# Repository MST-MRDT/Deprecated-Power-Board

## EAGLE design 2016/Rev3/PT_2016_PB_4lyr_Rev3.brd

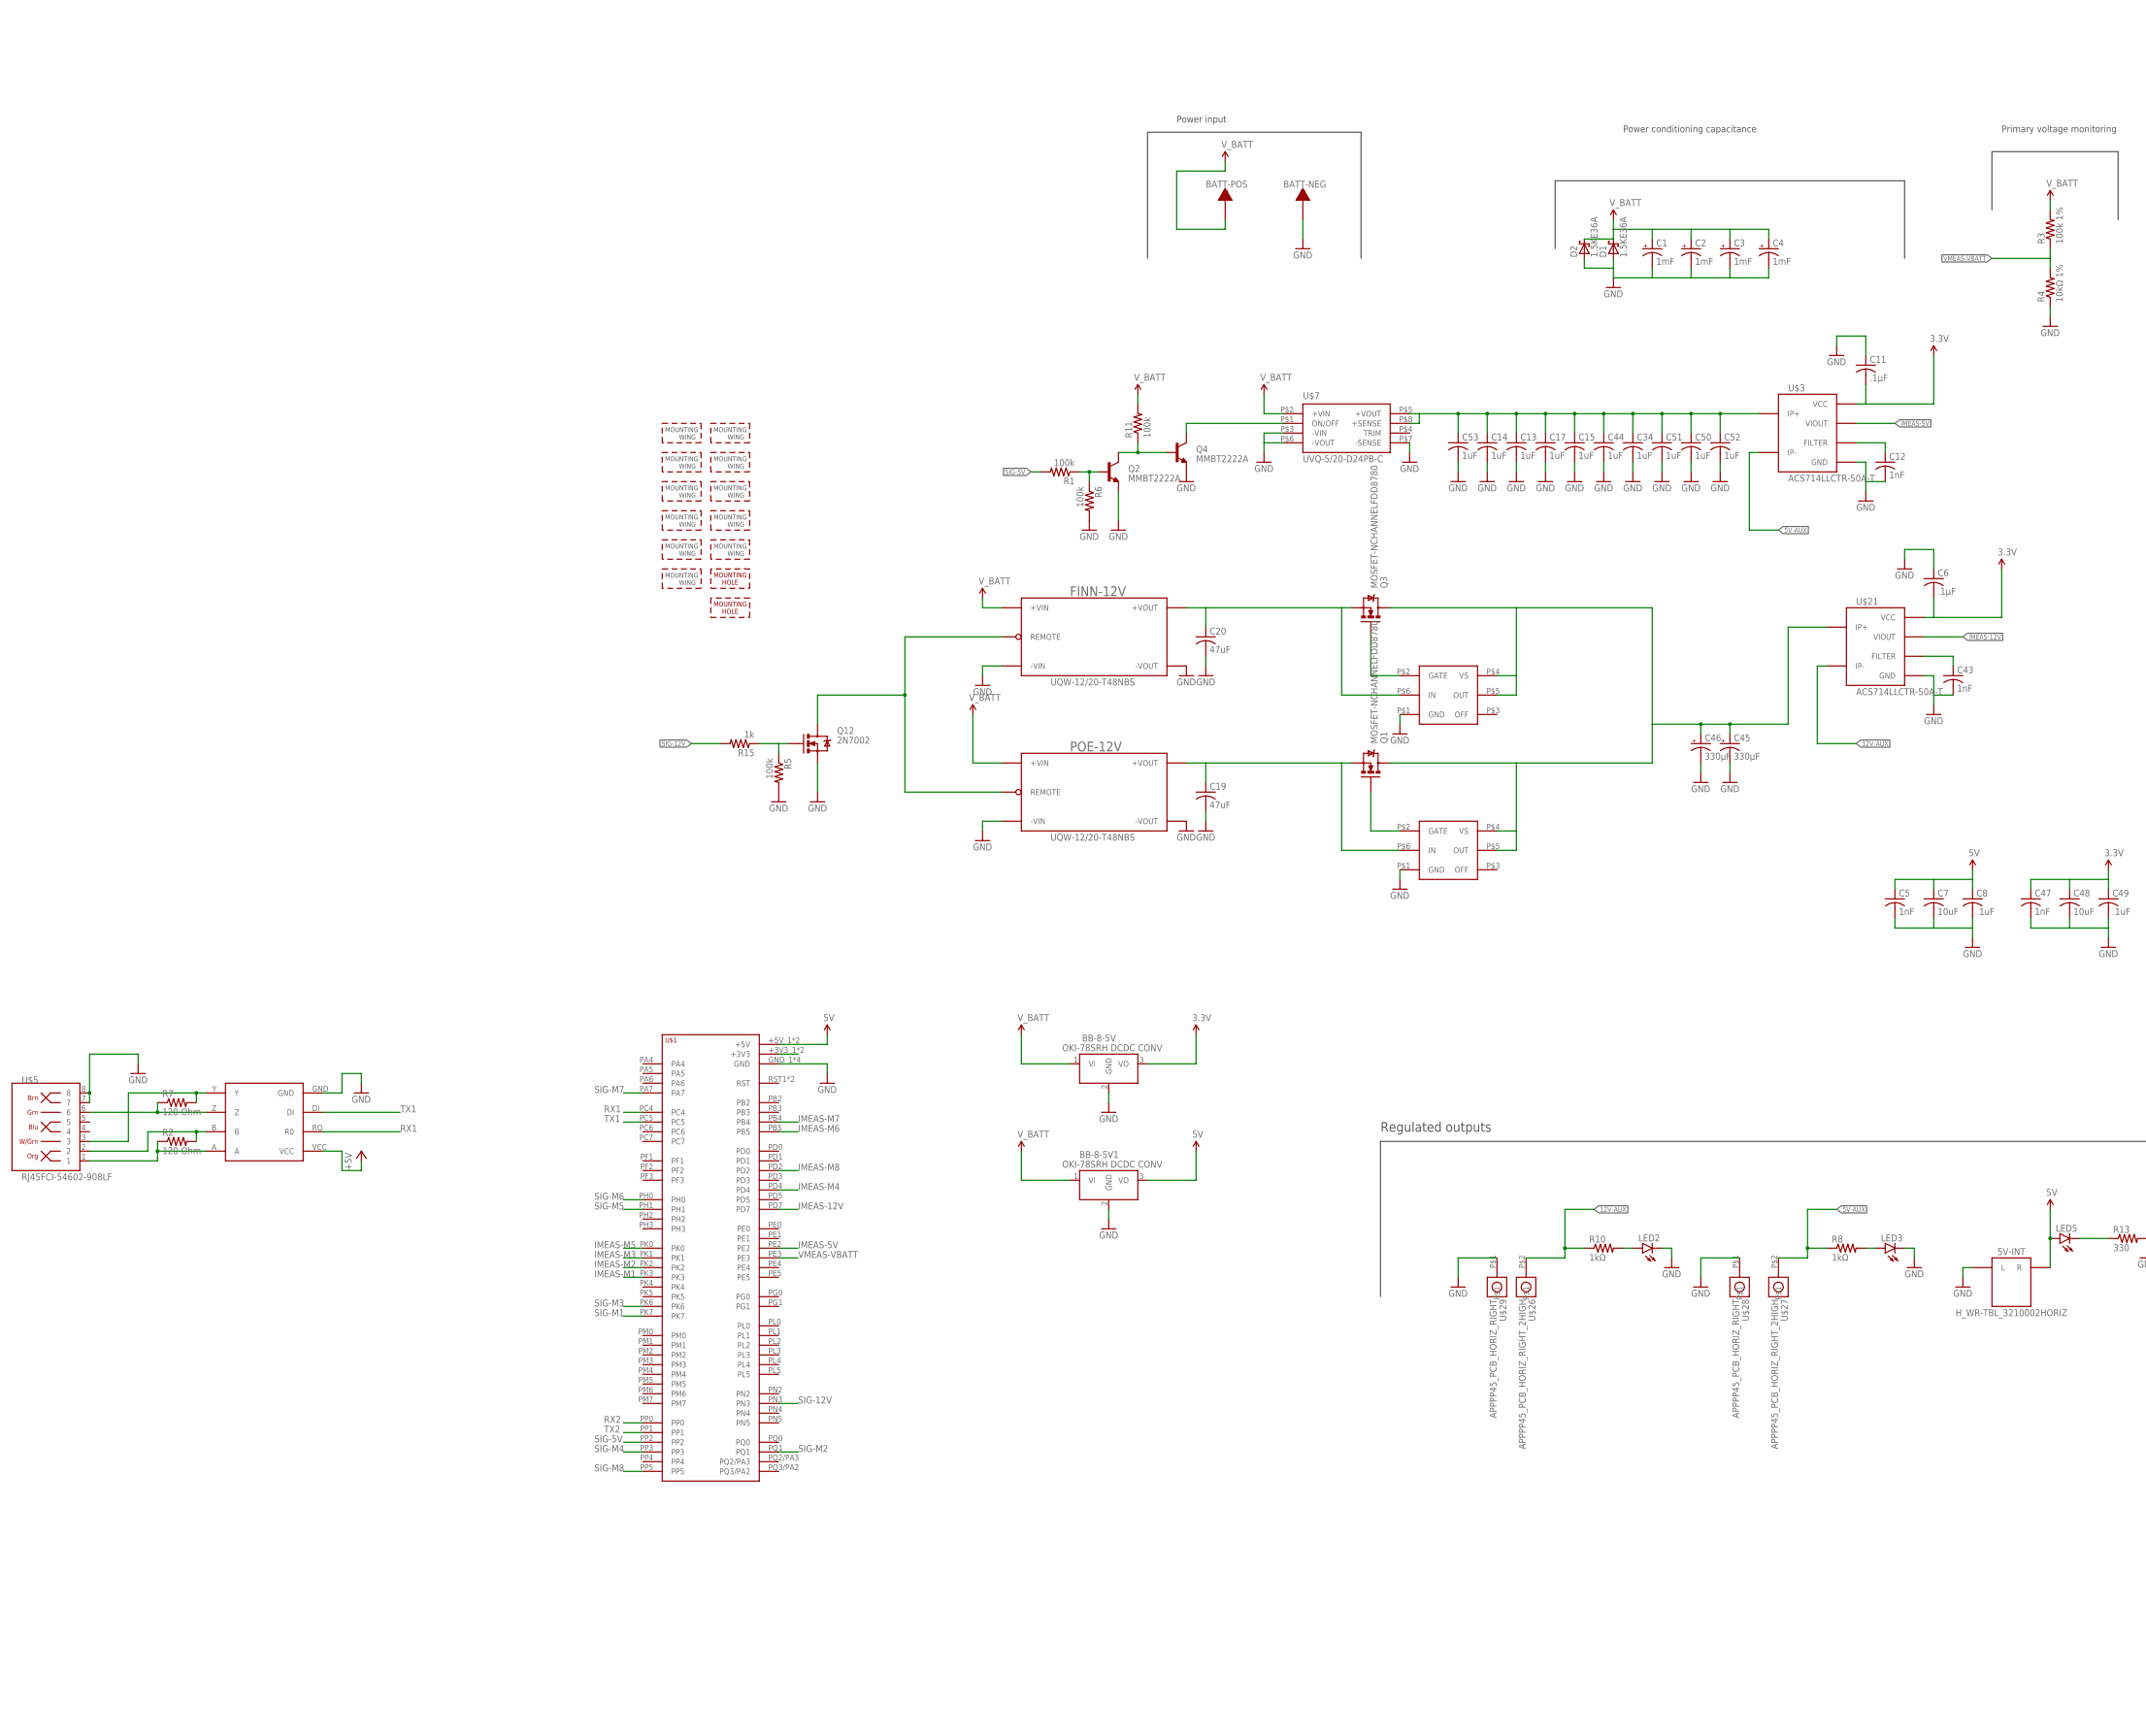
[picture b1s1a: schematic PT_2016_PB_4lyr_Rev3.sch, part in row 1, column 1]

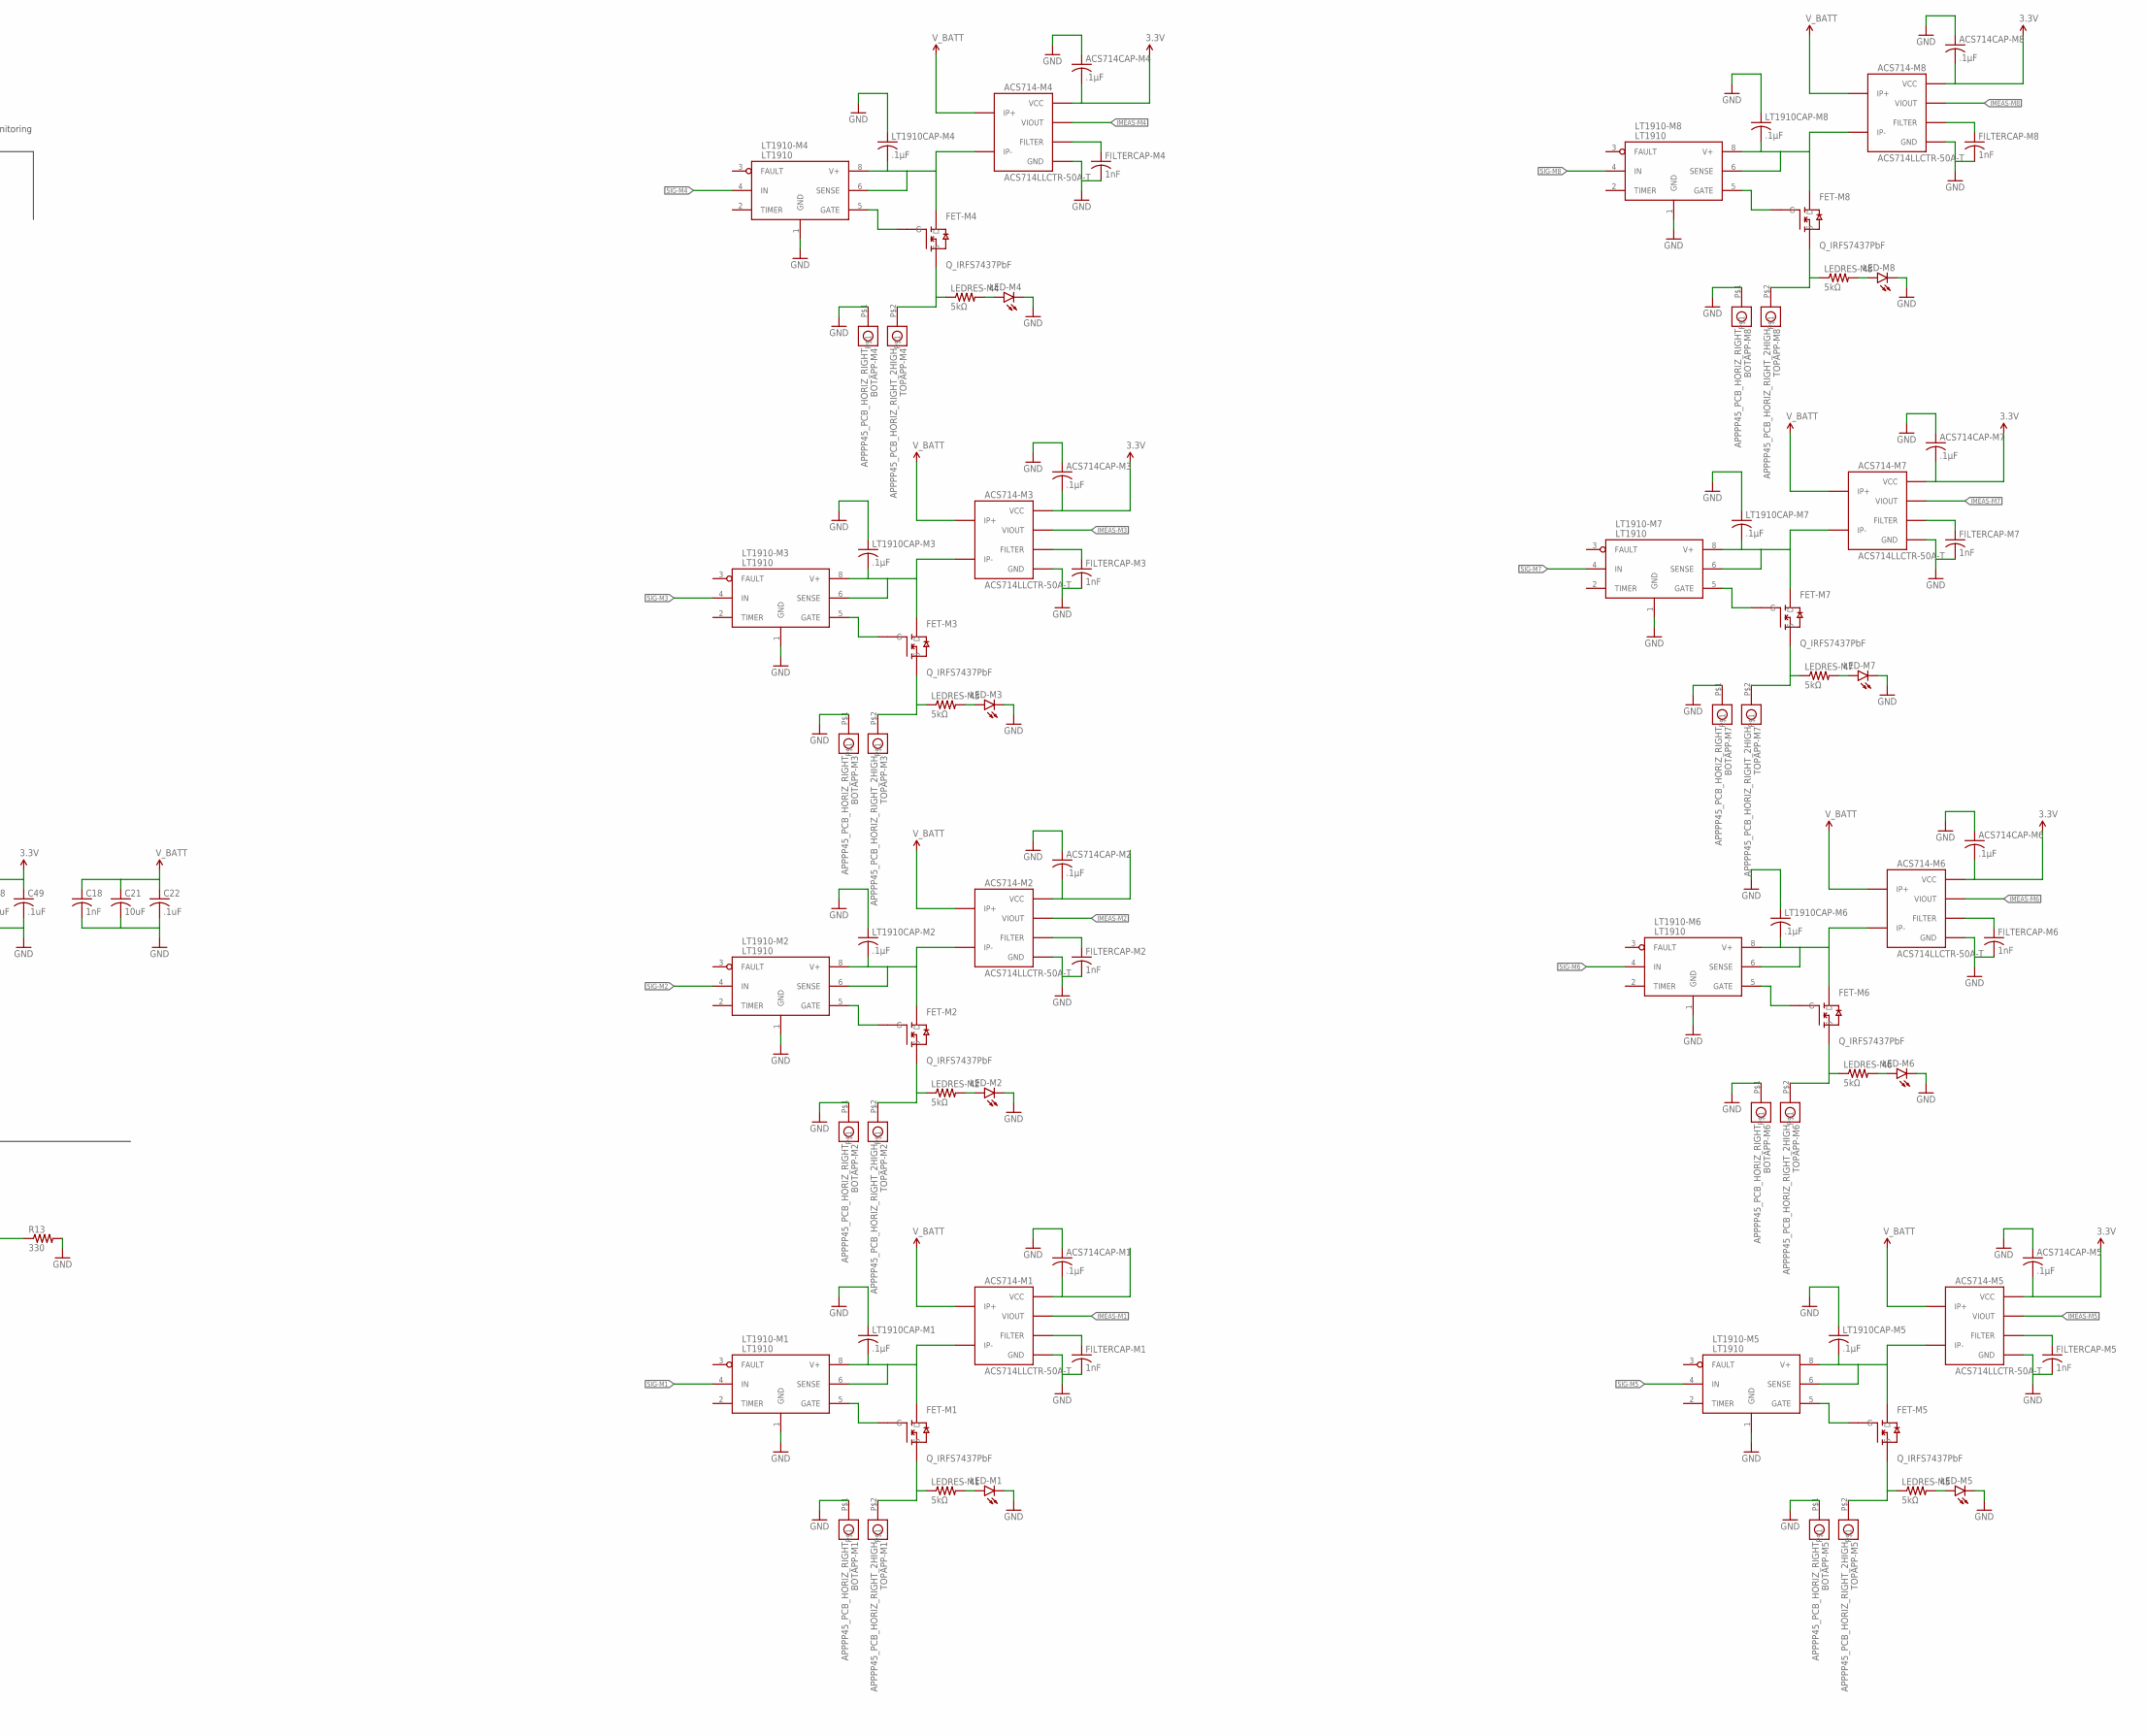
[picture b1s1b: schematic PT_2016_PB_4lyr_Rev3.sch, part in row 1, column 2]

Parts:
5V-INT: H_WR-TBL_3210002HORIZ; 691322110002
ACS714-M1, ACS714-M2, ACS714-M3, ACS714-M4, ACS714-M5, ACS714-M6, ACS714-M7, ACS714-M8: ACS714LLCTR-50A-T; SOIC8_ACS711
ACS714CAP-M1, ACS714CAP-M2, ACS714CAP-M3, ACS714CAP-M4, ACS714CAP-M5, ACS714CAP-M6, ACS714CAP-M7, ACS714CAP-M8: .1µF; C1206
BATT-NEG: TERMINAL_HOLE; LARGE_TERMINAL_HOLE
BATT-POS: TERMINAL_HOLE; LARGE_TERMINAL_HOLE
BB-8-5V, BB-8-5V1: Q_OKI-78SR; OKI-78SR_HORIZ
BOTAPP-M1, BOTAPP-M2, BOTAPP-M3, BOTAPP-M4, BOTAPP-M5, BOTAPP-M6, BOTAPP-M7, BOTAPP-M8: APPPP45_PCB_HORIZ_RIGHT; APP45_PCB_HORIZ_RIGHT
C1, C2, C3, C4: 1mF; C_12.5MM
C5, C12, C18, C43, C47: 1nF; C1206
C6, C11: .1µF; C1206
C7, C21, C48: 10uF; C1206
C8, C22, C49: .1uF; C1206
C13, C14, C15, C17, C34, C44, C50, C51, C52, C53: 1uF; C1206
C19, C20: 47uF; C1206
C45, C46: 330µF; E5-8,5
D1, D2: 1.5KE36A; CB429-17
FET-M1, FET-M2, FET-M3, FET-M4, FET-M5, FET-M6, FET-M7, FET-M8: Q_IRFS7437PbF; D2PACK
FILTERCAP-M1, FILTERCAP-M2, FILTERCAP-M3, FILTERCAP-M4, FILTERCAP-M5, FILTERCAP-M6, FILTERCAP-M7, FILTERCAP-M8: 1nF; C1206
FINN-12V: UQW-12/20-T48NBS; U-T48-QB-NO_TRIM
LED2, LED3, LED5: LED1206; LED-1206
LED-M1, LED-M2, LED-M3, LED-M4, LED-M5, LED-M6, LED-M7, LED-M8: LED1206; LED-1206
LEDRES-M1, LEDRES-M2, LEDRES-M3, LEDRES-M4, LEDRES-M5, LEDRES-M6, LEDRES-M7, LEDRES-M8: 5kΩ; 1206
LT1910-M1, LT1910-M2, LT1910-M3, LT1910-M4, LT1910-M5, LT1910-M6, LT1910-M7, LT1910-M8: LT1910; SO8
LT1910CAP-M1, LT1910CAP-M2, LT1910CAP-M3, LT1910CAP-M4, LT1910CAP-M5, LT1910CAP-M6, LT1910CAP-M7, LT1910CAP-M8: .1µF; C1206
POE-12V: UQW-12/20-T48NBS; U-T48-QB-NO_TRIM
Q1, Q3: MOSFET-NCHANNELFDD8780; DPAK
Q2, Q4: MMBT2222A; SOT23-3
Q12: 2N7002; SOT323
R1, R6, R11: 100k; 1206
R2, R7: 120 Ohm; 1206
R3: 100k 1%; R1206
R4: 10kΩ 1%; R1206
R5: 100k; R1206
R8, R10: 1kΩ; 1206
R13: 330; 1206
R15: 1k; R1206
TOPAPP-M1, TOPAPP-M2, TOPAPP-M3, TOPAPP-M4, TOPAPP-M5, TOPAPP-M6, TOPAPP-M7, TOPAPP-M8: APPPP45_PCB_HORIZ_RIGHT_2HIGH; APP45_PCB_HORIZ_RIGHT_2HIGH
U$1: TIVA-C-CONNECTED
U$2, U$4, U$25, U$30, U$31, U$32, U$33, U$34, U$35, U$41, U$42: APP_MOUTING_WINGHORIZ; APP45_MOUNTING_WING_HORIZ
U$3, U$21: ACS714LLCTR-50A-T; SOIC8_ACS711
U$5: RJ45FCI-54602-908LF; FCI-54602-908LF
U$6, U$9: LM5050
U$7: UVQ-5/20-D24PB-C; MURATA_5V_DC-DC_CONVERTER
U$8, U$10: MOUNTING_HOLE#8; #8_SCREW
U$24: MAX3077; MAX3070E
U$26, U$27: APPPP45_PCB_HORIZ_RIGHT_2HIGH; APP45_PCB_HORIZ_RIGHT_2HIGH
U$28, U$29: APPPP45_PCB_HORIZ_RIGHT; APP45_PCB_HORIZ_RIGHT

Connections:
3.3V: ACS714-M1.8 (VCC), ACS714-M2.8 (VCC), ACS714-M3.8 (VCC), ACS714-M4.8 (VCC), ACS714-M5.8 (VCC), ACS714-M6.8 (VCC), ACS714-M7.8 (VCC), ACS714-M8.8 (VCC), ACS714CAP-M1.2, ACS714CAP-M2.2, ACS714CAP-M3.2, ACS714CAP-M4.2, ACS714CAP-M5.2, ACS714CAP-M6.2, ACS714CAP-M7.2, ACS714CAP-M8.2, BB-8-5V.3 (VO), C6.2, C11.2, C47.1, C48.1, C49.1, U$3.8 (VCC), U$21.8 (VCC), U$24.VCC
5V: 5V-INT.R, BB-8-5V1.3 (VO), C5.1, C7.1, C8.1, LED5.A, U$1.+5V_1 (+5V), U$1.+5V_2 (+5V)
5V-AUX: R8.1, U$3.4 (IP-), U$27.P$2
12V-AUX: R10.1, U$21.4 (IP-), U$26.P$2
DRAIN-M1: ACS714-M1.4 (IP-), FET-M1.TAB (D), LT1910-M1.6 (SENSE), LT1910-M1.8 (V+), LT1910CAP-M1.2
DRAIN-M2: ACS714-M2.4 (IP-), FET-M2.TAB (D), LT1910-M2.6 (SENSE), LT1910-M2.8 (V+), LT1910CAP-M2.2
DRAIN-M3: ACS714-M3.4 (IP-), FET-M3.TAB (D), LT1910-M3.6 (SENSE), LT1910-M3.8 (V+), LT1910CAP-M3.2
DRAIN-M4: ACS714-M4.4 (IP-), FET-M4.TAB (D), LT1910-M4.6 (SENSE), LT1910-M4.8 (V+), LT1910CAP-M4.2
DRAIN-M5: ACS714-M5.4 (IP-), FET-M5.TAB (D), LT1910-M5.6 (SENSE), LT1910-M5.8 (V+), LT1910CAP-M5.2
DRAIN-M6: ACS714-M6.4 (IP-), FET-M6.TAB (D), LT1910-M6.6 (SENSE), LT1910-M6.8 (V+), LT1910CAP-M6.2
DRAIN-M7: ACS714-M7.4 (IP-), FET-M7.TAB (D), LT1910-M7.6 (SENSE), LT1910-M7.8 (V+), LT1910CAP-M7.2
DRAIN-M8: ACS714-M8.4 (IP-), FET-M8.TAB (D), LT1910-M8.6 (SENSE), LT1910-M8.8 (V+), LT1910CAP-M8.2
FILTER-M1: ACS714-M1.6 (FILTER), FILTERCAP-M1.1
FILTER-M2: ACS714-M2.6 (FILTER), FILTERCAP-M2.1
FILTER-M3: ACS714-M3.6 (FILTER), FILTERCAP-M3.1
FILTER-M4: ACS714-M4.6 (FILTER), FILTERCAP-M4.1
FILTER-M5: ACS714-M5.6 (FILTER), FILTERCAP-M5.1
FILTER-M6: ACS714-M6.6 (FILTER), FILTERCAP-M6.1
FILTER-M7: ACS714-M7.6 (FILTER), FILTERCAP-M7.1
FILTER-M8: ACS714-M8.6 (FILTER), FILTERCAP-M8.1
GATE-M1: FET-M1.1 (G), LT1910-M1.5 (GATE)
GATE-M2: FET-M2.1 (G), LT1910-M2.5 (GATE)
GATE-M3: FET-M3.1 (G), LT1910-M3.5 (GATE)
GATE-M4: FET-M4.1 (G), LT1910-M4.5 (GATE)
GATE-M5: FET-M5.1 (G), LT1910-M5.5 (GATE)
GATE-M6: FET-M6.1 (G), LT1910-M6.5 (GATE)
GATE-M7: FET-M7.1 (G), LT1910-M7.5 (GATE)
GATE-M8: FET-M8.1 (G), LT1910-M8.5 (GATE)
GND: 5V-INT.L, ACS714-M1.5 (GND), ACS714-M2.5 (GND), ACS714-M3.5 (GND), ACS714-M4.5 (GND), ACS714-M5.5 (GND), ACS714-M6.5 (GND), ACS714-M7.5 (GND), ACS714-M8.5 (GND), ACS714CAP-M1.1, ACS714CAP-M2.1, ACS714CAP-M3.1, ACS714CAP-M4.1, ACS714CAP-M5.1, ACS714CAP-M6.1, ACS714CAP-M7.1, ACS714CAP-M8.1, BATT-NEG.P$1, BB-8-5V.2 (GND), BB-8-5V1.2 (GND), BOTAPP-M1.P$1, BOTAPP-M2.P$1, BOTAPP-M3.P$1, BOTAPP-M4.P$1, BOTAPP-M5.P$1, BOTAPP-M6.P$1, BOTAPP-M7.P$1, BOTAPP-M8.P$1, C1.-, C2.-, C3.-, C4.-, C5.2, C6.1, C7.2, C8.2, C11.1, C12.2, C13.2, C14.2, C15.2, C17.2, C18.2, C19.2, C20.2, C21.2, C22.2, C34.2, C43.2, C44.2, C45.-, C46.-, C47.2, C48.2, C49.2, C50.2, C51.2, C52.2, C53.2, D1.A, D2.A, FILTERCAP-M1.2, FILTERCAP-M2.2, FILTERCAP-M3.2, FILTERCAP-M4.2, FILTERCAP-M5.2, FILTERCAP-M6.2, FILTERCAP-M7.2, FILTERCAP-M8.2, FINN-12V.3 (-VIN), FINN-12V.4 (-VOUT), LED2.C, LED3.C, LED-M1.C, LED-M2.C, LED-M3.C, LED-M4.C, LED-M5.C, LED-M6.C, LED-M7.C, LED-M8.C, LT1910-M1.1 (GND), LT1910-M2.1 (GND), LT1910-M3.1 (GND), LT1910-M4.1 (GND), LT1910-M5.1 (GND), LT1910-M6.1 (GND), LT1910-M7.1 (GND), LT1910-M8.1 (GND), LT1910CAP-M1.1, LT1910CAP-M2.1, LT1910CAP-M3.1, LT1910CAP-M4.1, LT1910CAP-M5.1, LT1910CAP-M6.1, LT1910CAP-M7.1, LT1910CAP-M8.1, POE-12V.3 (-VIN), POE-12V.4 (-VOUT), Q2.2 (E), Q4.2 (E), Q12.2 (S), R4.1, R5.2, R6.2, R13.2, U$1.GND_1 (GND), U$1.GND_2 (GND), U$1.GND_3 (GND), U$1.GND_4 (GND), U$3.5 (GND), U$5.7, U$5.8, U$6.P$1 (GND), U$7.P$3 (-VIN), U$7.P$6 (-VOUT), U$7.P$7 (-SENSE), U$9.P$1 (GND), U$21.5 (GND), U$24.GND, U$28.P$1, U$29.P$1
IMEAS-5V: U$1.PE2, U$3.7 (VIOUT)
IMEAS-12V: U$1.PD7, U$21.7 (VIOUT)
IMEAS-M1: ACS714-M1.7 (VIOUT), U$1.PK3
IMEAS-M2: ACS714-M2.7 (VIOUT), U$1.PK2
IMEAS-M3: ACS714-M3.7 (VIOUT), U$1.PK1
IMEAS-M4: ACS714-M4.7 (VIOUT), U$1.PD4
IMEAS-M5: ACS714-M5.7 (VIOUT), U$1.PK0
IMEAS-M6: ACS714-M6.7 (VIOUT), U$1.PB5
IMEAS-M7: ACS714-M7.7 (VIOUT), U$1.PB4
IMEAS-M8: ACS714-M8.7 (VIOUT), U$1.PD2
LEDLINE-M1: LED-M1.A, LEDRES-M1.2
LEDLINE-M2: LED-M2.A, LEDRES-M2.2
LEDLINE-M3: LED-M3.A, LEDRES-M3.2
LEDLINE-M4: LED-M4.A, LEDRES-M4.2
LEDLINE-M5: LED-M5.A, LEDRES-M5.2
LEDLINE-M6: LED-M6.A, LEDRES-M6.2
LEDLINE-M7: LED-M7.A, LEDRES-M7.2
LEDLINE-M8: LED-M8.A, LEDRES-M8.2
unnamed: C20.1, FINN-12V.8 (+VOUT), Q3.3 (S), U$6.P$6 (IN)
unnamed: C19.1, POE-12V.8 (+VOUT), Q1.3 (S), U$9.P$6 (IN)
unnamed: Q3.1 (G), U$6.P$2 (GATE)
unnamed: FINN-12V.2 (REMOTE), POE-12V.2 (REMOTE), Q12.3 (D)
unnamed: Q1.1 (G), U$9.P$2 (GATE)
unnamed: LED5.C, R13.1
unnamed: Q4.3 (C), U$7.P$1 (ON/OFF)
unnamed: C43.1, U$21.6 (FILTER)
unnamed: Q2.1 (B), R1.1, R6.1
unnamed: Q2.3 (C), Q4.1 (B), R11.1
unnamed: C45.+, C46.+, Q1.4 (D), Q3.4 (D), U$6.P$4 (VS), U$6.P$5 (OUT), U$9.P$4 (VS), U$9.P$5 (OUT), U$21.1 (IP+)
unnamed: LED3.A, R8.2
unnamed: C12.1, U$3.6 (FILTER)
unnamed: LED2.A, R10.2
unnamed: C13.1, C14.1, C15.1, C17.1, C34.1, C44.1, C50.1, C51.1, C52.1, C53.1, U$3.1 (IP+), U$7.P$5 (+VOUT), U$7.P$8 (+SENSE)
unnamed: U$1.+3V3_1 (+3V3), U$1.+3V3_2 (+3V3)
unnamed: Q12.1 (G), R5.1, R15.1
REC+1: R2.1, U$5.1, U$24.A
REC-1: R2.2, U$5.2, U$24.B
RX1: U$1.PC4, U$24.RO (R0)
RX2: U$1.PP0
SIG-5V: R1.2, U$1.PP2
SIG-12V: R15.2, U$1.PN3
SIG-M1: LT1910-M1.4 (IN), U$1.PK7
SIG-M2: LT1910-M2.4 (IN), U$1.PQ1
SIG-M3: LT1910-M3.4 (IN), U$1.PK6
SIG-M4: LT1910-M4.4 (IN), U$1.PP3
SIG-M5: LT1910-M5.4 (IN), U$1.PH1
SIG-M6: LT1910-M6.4 (IN), U$1.PH0
SIG-M7: LT1910-M7.4 (IN), U$1.PA7
SIG-M8: LT1910-M8.4 (IN), U$1.PP5
SOURCE-M1: FET-M1.2 (S), LEDRES-M1.1, TOPAPP-M1.P$2
SOURCE-M2: FET-M2.2 (S), LEDRES-M2.1, TOPAPP-M2.P$2
SOURCE-M3: FET-M3.2 (S), LEDRES-M3.1, TOPAPP-M3.P$2
SOURCE-M4: FET-M4.2 (S), LEDRES-M4.1, TOPAPP-M4.P$2
SOURCE-M5: FET-M5.2 (S), LEDRES-M5.1, TOPAPP-M5.P$2
SOURCE-M6: FET-M6.2 (S), LEDRES-M6.1, TOPAPP-M6.P$2
SOURCE-M7: FET-M7.2 (S), LEDRES-M7.1, TOPAPP-M7.P$2
SOURCE-M8: FET-M8.2 (S), LEDRES-M8.1, TOPAPP-M8.P$2
TRANS+1: R7.2, U$5.3, U$24.Y
TRANS-1: R7.1, U$5.6, U$24.Z
TX1: U$1.PC5, U$24.DI
TX2: U$1.PP1
VMEAS-VBATT: R3.1, R4.2, U$1.PE3
V_BATT: ACS714-M1.1 (IP+), ACS714-M2.1 (IP+), ACS714-M3.1 (IP+), ACS714-M4.1 (IP+), ACS714-M5.1 (IP+), ACS714-M6.1 (IP+), ACS714-M7.1 (IP+), ACS714-M8.1 (IP+), BATT-POS.P$1, BB-8-5V.1 (VI), BB-8-5V1.1 (VI), C1.+, C2.+, C3.+, C4.+, C18.1, C21.1, C22.1, D1.C, D2.C, FINN-12V.1 (+VIN), POE-12V.1 (+VIN), R3.2, R11.2, U$7.P$2 (+VIN)

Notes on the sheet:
Primary voltage monitoring
Power conditioning capacitance
Power input
Regulated outputs

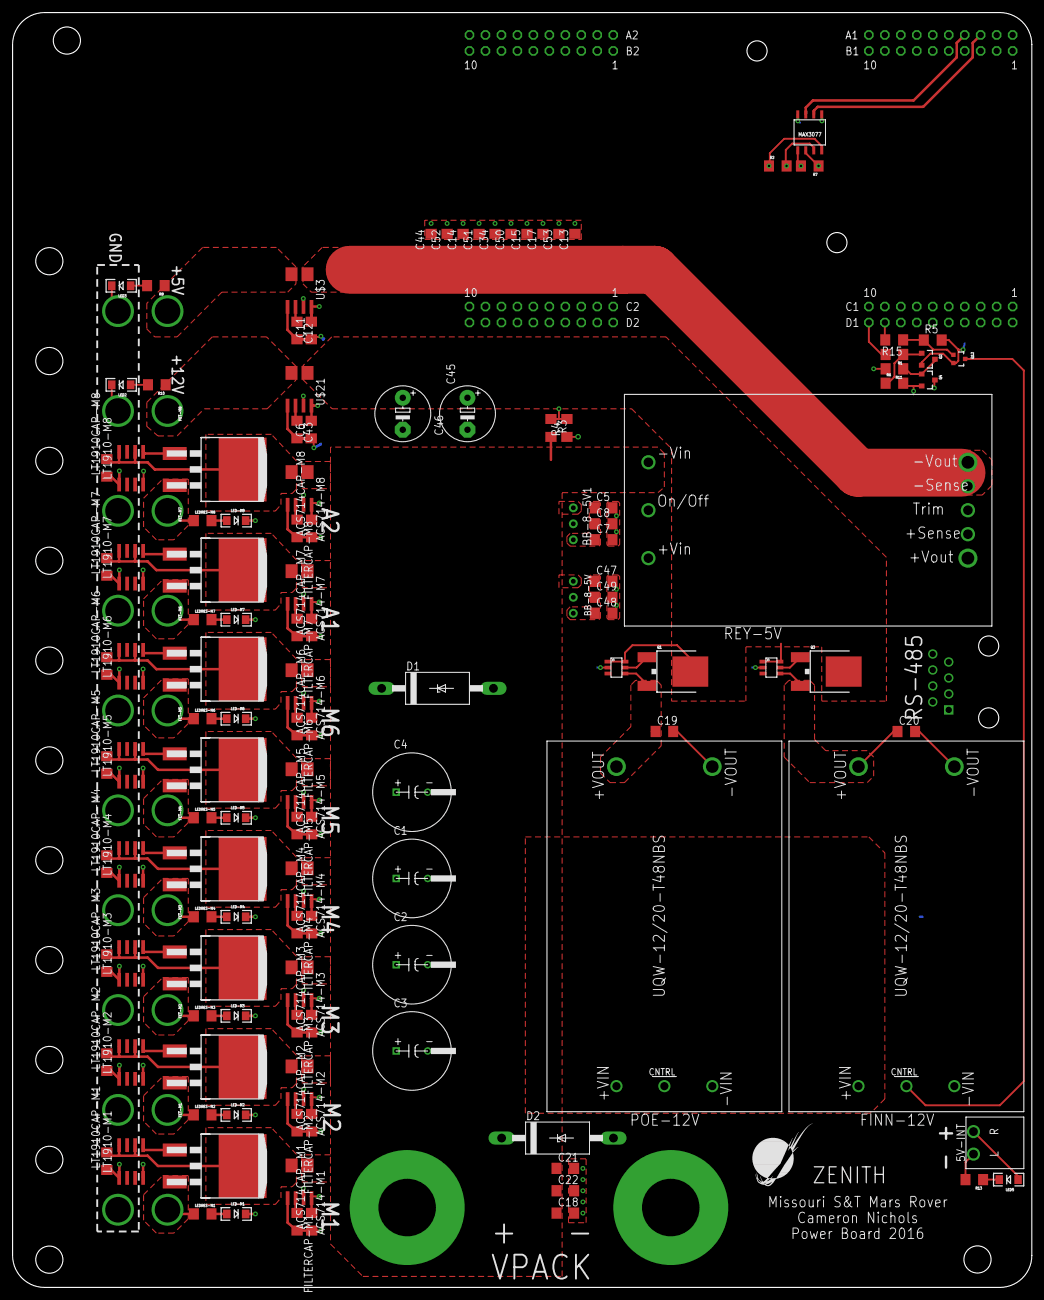
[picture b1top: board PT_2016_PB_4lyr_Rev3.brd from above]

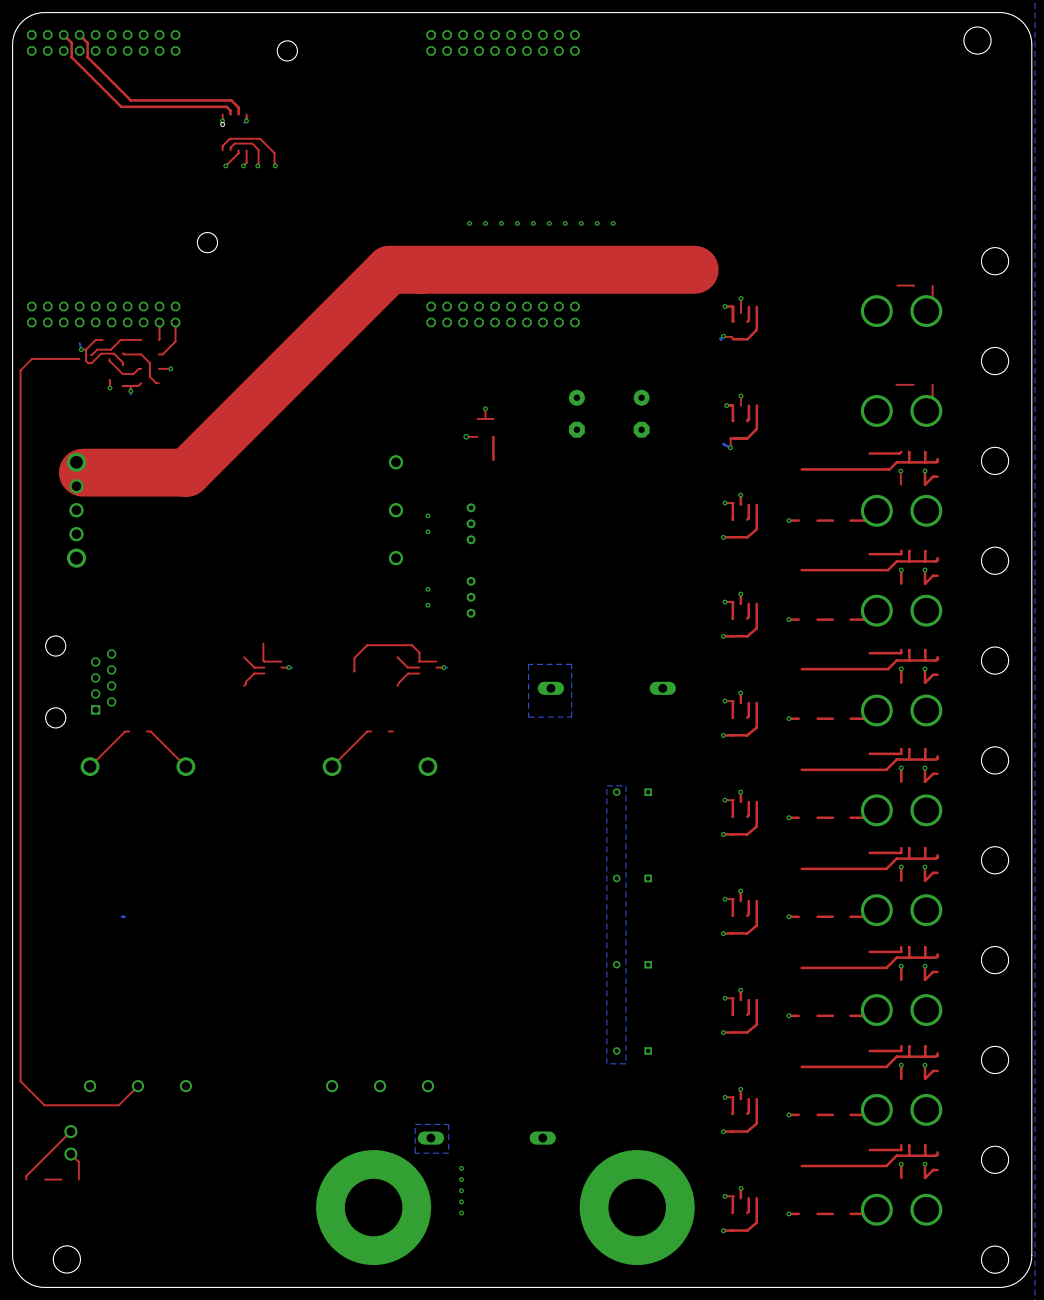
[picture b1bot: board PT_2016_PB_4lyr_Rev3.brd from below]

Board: 4 copper layers, 162.1 x 202.7 mm, 166 parts (11 on the bottom side), 90 nets.

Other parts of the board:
U$22: MRDT_LOGO

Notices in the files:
parts and their libraries:
SparkFun-Passives: Licensing: CC v3.0 Share-Alike You are welcome to use this library for commercial purposes.
SparkFun-LED: Licensing: Creative Commons ShareAlike 4.0 International - https://creativecommons.org/licenses/by-sa/4.0
